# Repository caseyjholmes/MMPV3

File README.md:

# MMPV3
Updated Holmes Modular 5 channel Mute Mix Pan Eurorack format mixer now with Stereo Outs and PSI POWER for 2023

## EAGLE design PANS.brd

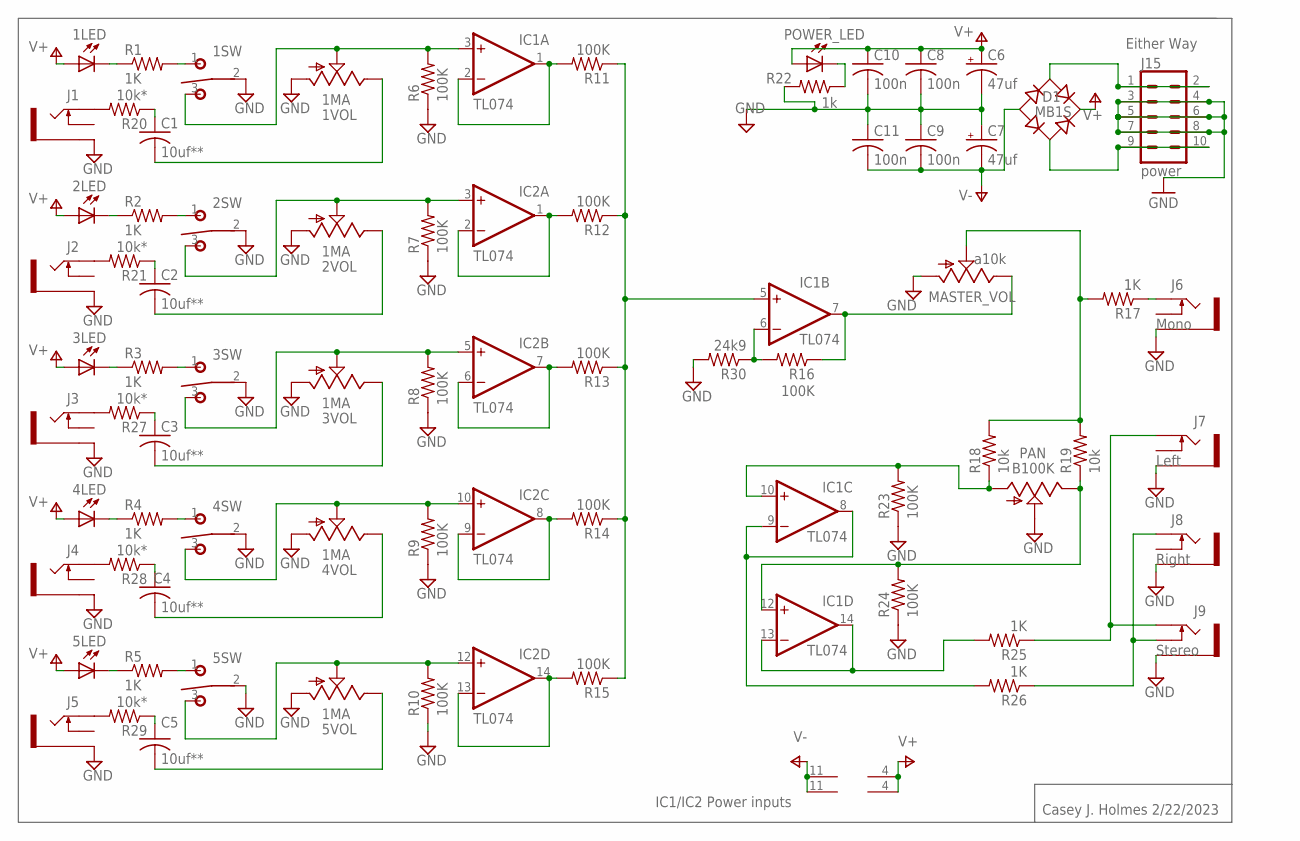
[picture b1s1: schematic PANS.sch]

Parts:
1LED, 2LED, 3LED, 4LED, 5LED: green; LED5MM
1SW, 2SW, 3SW, 4SW, 5SW: on/on; M9040P
1VOL, 2VOL, 3VOL, 4VOL, 5VOL: 1MA; 9MM_SNAP-IN_POT
C1, C2, C3, C4, C5: 10uf**; C0805K
C6, C7: 47uf; PANASONIC_D
C8, C9, C10, C11: 100n; C0805
D1: MB1S; SOIC-4
IC1, IC2: TL074; SO14
J1, J2, J3, J4, J5, J6, J8: THONKICONNNEW; WQP-PJ301M-12_JACK
J7: LEFT; WQP-PJ301M-12_JACK
J9: Stereo; WQP-PJ301M-12_JACK
J15: power; 2X5
MASTER_VOL: a10k; 9MM_SNAP-IN_POT
PAN: B100K; 9MM_SNAP-IN_POT
POWER_LED: green; LED5MM
R1, R2, R3, R4, R5, R17, R25, R26: 1K; M0805
R6, R7, R8, R9, R10, R11, R12, R13, R14, R15, R16, R23, R24: 100K; M0805
R18, R19: 10k; M0805
R20, R21, R27, R28, R29: 10k*; M0805
R22: 1k; M0805
R30: 24k9; M0805

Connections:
C2: J2.P$1_TIP (TIP), R21.2
GND: 1SW.2, 1VOL.1 (A), 2SW.2, 2VOL.1 (A), 3SW.2, 3VOL.1 (A), 4SW.2, 4VOL.1 (A), 5SW.2, 5VOL.1 (A), C6.-, C7.+, C8.2, C9.1, C10.2, C11.1, J1.P$3_SLEEVE (SLEEVE), J2.P$3_SLEEVE (SLEEVE), J3.P$3_SLEEVE (SLEEVE), J4.P$3_SLEEVE (SLEEVE), J5.P$3_SLEEVE (SLEEVE), J6.P$3_SLEEVE (SLEEVE), J7.P$3_SLEEVE (SLEEVE), J8.P$3_SLEEVE (SLEEVE), J9.P$3_SLEEVE (SLEEVE), J15.3, J15.4, J15.5, J15.6, J15.7, J15.8, MASTER_VOL.1 (A), PAN.2 (S), R6.1, R7.1, R8.1, R9.1, R10.1, R22.2, R23.1, R24.1, R30.2
IC1: IC1.1 (OUT), IC1.2 (-IN), R11.2
unnamed: J7.P$1_TIP (TIP), J9.P$1_TIP (TIP), R25.1
unnamed: J1.P$1_TIP (TIP), R20.2
unnamed: 1SW.1 (O), R1.2
unnamed: 1LED.K (C), R1.1
unnamed: 1VOL.3 (E), C1.2
unnamed: 2SW.1 (O), R2.2
unnamed: 2LED.K (C), R2.1
unnamed: 4LED.K (C), R4.1
unnamed: 1SW.3 (S), 1VOL.2 (S), IC1.3 (+IN), R6.2
unnamed: 5LED.K (C), R5.1
unnamed: 3LED.K (C), R3.1
unnamed: 5SW.1 (O), R5.2
unnamed: J4.P$1_TIP (TIP), R28.2
unnamed: 3SW.1 (O), R3.2
unnamed: 4SW.1 (O), R4.2
unnamed: J5.P$1_TIP (TIP), R29.2
unnamed: IC1.6 (-IN), R16.2, R30.1
unnamed: 2VOL.3 (E), C2.2
unnamed: 3VOL.3 (E), C3.2
unnamed: 4VOL.3 (E), C4.2
unnamed: 5VOL.3 (E), C5.2
unnamed: 2SW.3 (S), 2VOL.2 (S), IC2.3 (+IN), R7.2
unnamed: 3SW.3 (S), 3VOL.2 (S), IC2.5 (+IN), R8.2
unnamed: 4SW.3 (S), 4VOL.2 (S), IC2.10 (+IN), R9.2
unnamed: 5SW.3 (S), 5VOL.2 (S), IC2.12 (+IN), R10.2
unnamed: J8.P$1_TIP (TIP), J9.P$2_SWITCH (SWITCH), R26.1
unnamed: IC2.1 (OUT), IC2.2 (-IN), R12.2
unnamed: IC2.6 (-IN), IC2.7 (OUT), R13.2
unnamed: IC2.8 (OUT), IC2.9 (-IN), R14.2
unnamed: IC2.13 (-IN), IC2.14 (OUT), R15.2
unnamed: IC1.5 (+IN), R11.1, R12.1, R13.1, R14.1, R15.1
unnamed: POWER_LED.K (C), R22.1
unnamed: MASTER_VOL.2 (S), R17.2, R18.2, R19.2
unnamed: J6.P$1_TIP (TIP), R17.1
unnamed: C1.1, R20.1
unnamed: IC1.12 (+IN), PAN.3 (E), R19.1, R24.2
unnamed: C4.1, R28.1
unnamed: IC1.10 (+IN), PAN.1 (A), R18.1, R23.2
unnamed: IC1.8 (OUT), IC1.9 (-IN), R26.2
unnamed: IC1.13 (-IN), IC1.14 (OUT), R25.2
unnamed: IC1.7 (OUT), MASTER_VOL.3 (E), R16.1
unnamed: C5.1, R29.1
unnamed: C2.1, R21.1
unnamed: C3.1, R27.1
unnamed: J3.P$1_TIP (TIP), R27.2
unnamed: D1.~2 (AC2), J15.9, J15.10
SV1: D1.~1 (AC1), J15.1, J15.2
V+: 1LED.A, 2LED.A, 3LED.A, 4LED.A, 5LED.A, C6.+, C8.1, C10.1, D1.+, IC1.4 (V+), IC2.4 (V+), POWER_LED.A
V-: C7.-, C9.2, C11.2, D1.-, IC1.11 (V-), IC2.11 (V-)

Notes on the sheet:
IC1/IC2 Power inputs
Right
Left
Either Way
Stereo
Mono
Casey J. Holmes 2/22/2023

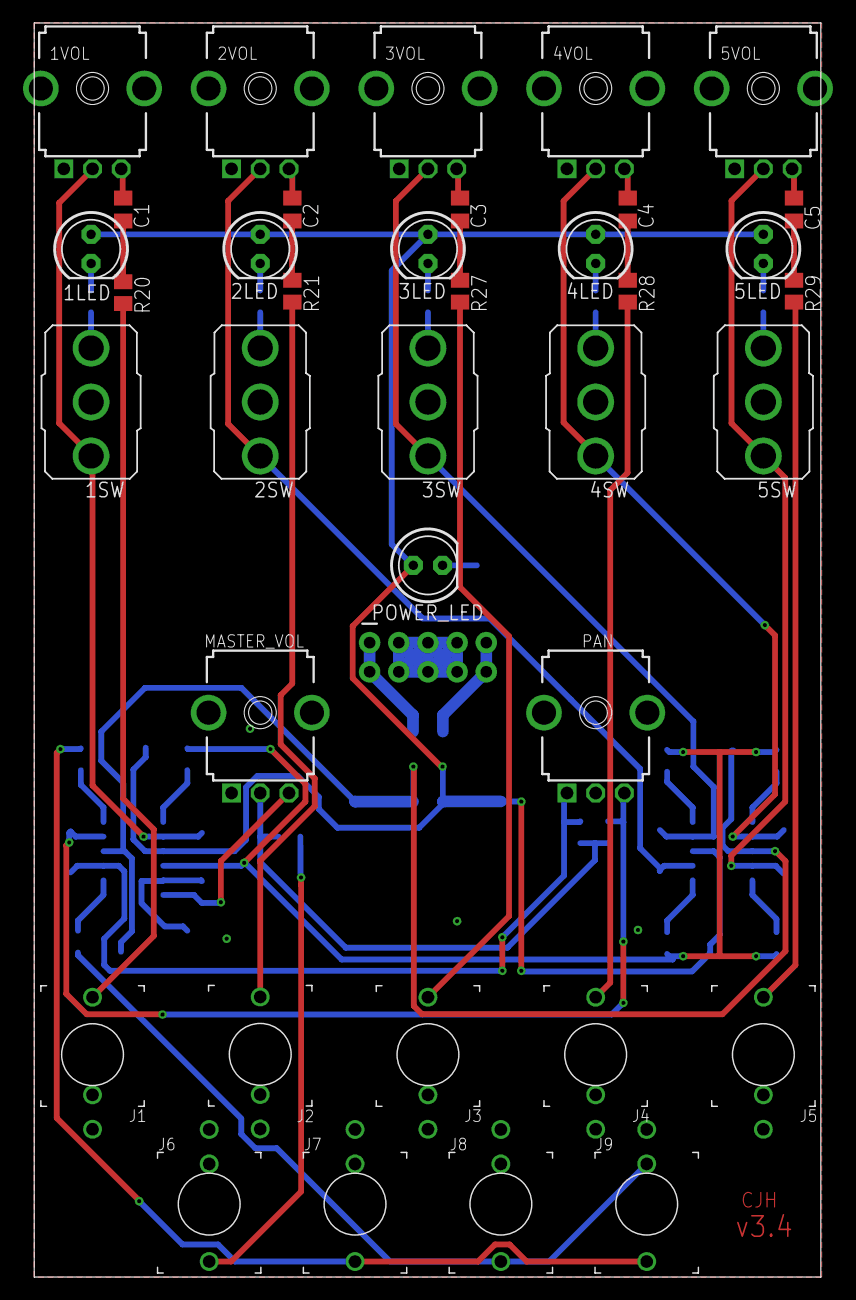
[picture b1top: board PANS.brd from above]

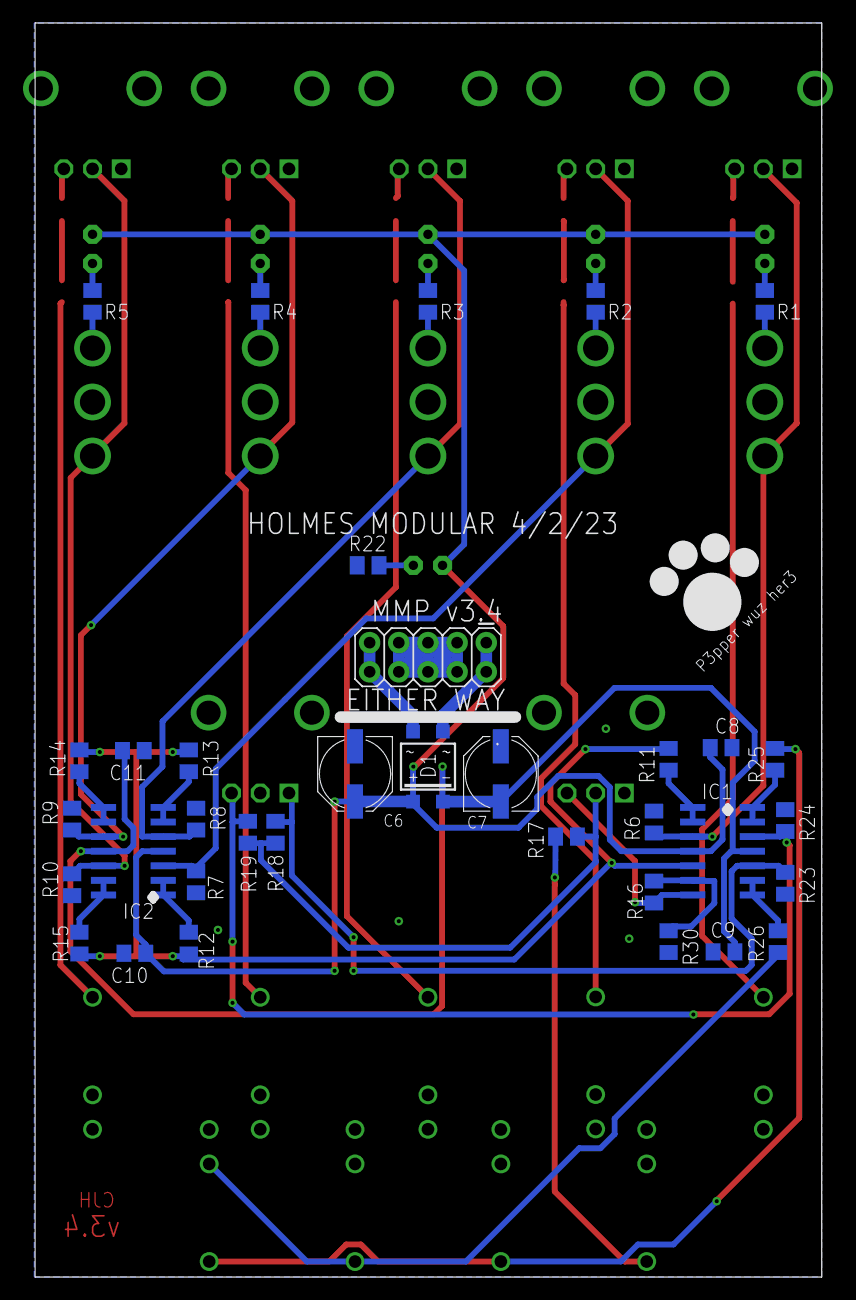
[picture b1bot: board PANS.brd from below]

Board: 2 copper layers, 68.5 x 109.2 mm, 72 parts (35 on the bottom side), 52 nets.

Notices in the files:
parts and their libraries:
SparkFun-Connectors: Licensing: Creative Commons ShareAlike 4.0 International - https://creativecommons.org/licenses/by-sa/4.0
